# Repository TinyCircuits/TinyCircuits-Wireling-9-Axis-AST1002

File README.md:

# TinyCircuits Wireling 9-Axis
# AST1002 Rev1

The design files are located under design_files/ for the TinyCircuits AST1002 Rev 1 PCB. This is a Wireling board which measures 9 degrees of freedom (9DOF) and features the ST LSM9DS1 - a system-in-package featuring a 3D digital linear acceleration sensor, a 3D digital angular rate sensor, and a 3D digital magnetic sensor.

Format is in Cadsoft Eagle format - Eagle version 6.2 was used for the original design.

For more infomation on this, check out the product page at TinyCircuits.com

# License:

Design by TinyCircuits.
All design files are released under the Creative Commons Attribution Share-Alike 3.0 License, see the following link for details: http://creativecommons.org/licenses/by-sa/3.0

All text above must be included in any redistribution or derived design

This project uses designs and concepts developed as part of the Arduino project and the LilyPad project.  The TinyCircuits design files themselves (schematics, PCB and libraries) are not directly derived from these works' design files and have been created new, however the concepts and basic architecture behind the TinyDuino and TinyLily products are derived and we thank the hard work of the organizations below for their contributions to open-source hardware:
  
Original Arduino Uno Design by Team Arduino

LilyPad Arduino Design by Leah Buechley and Sparkfun Electronics

Please support the open-source hardware community

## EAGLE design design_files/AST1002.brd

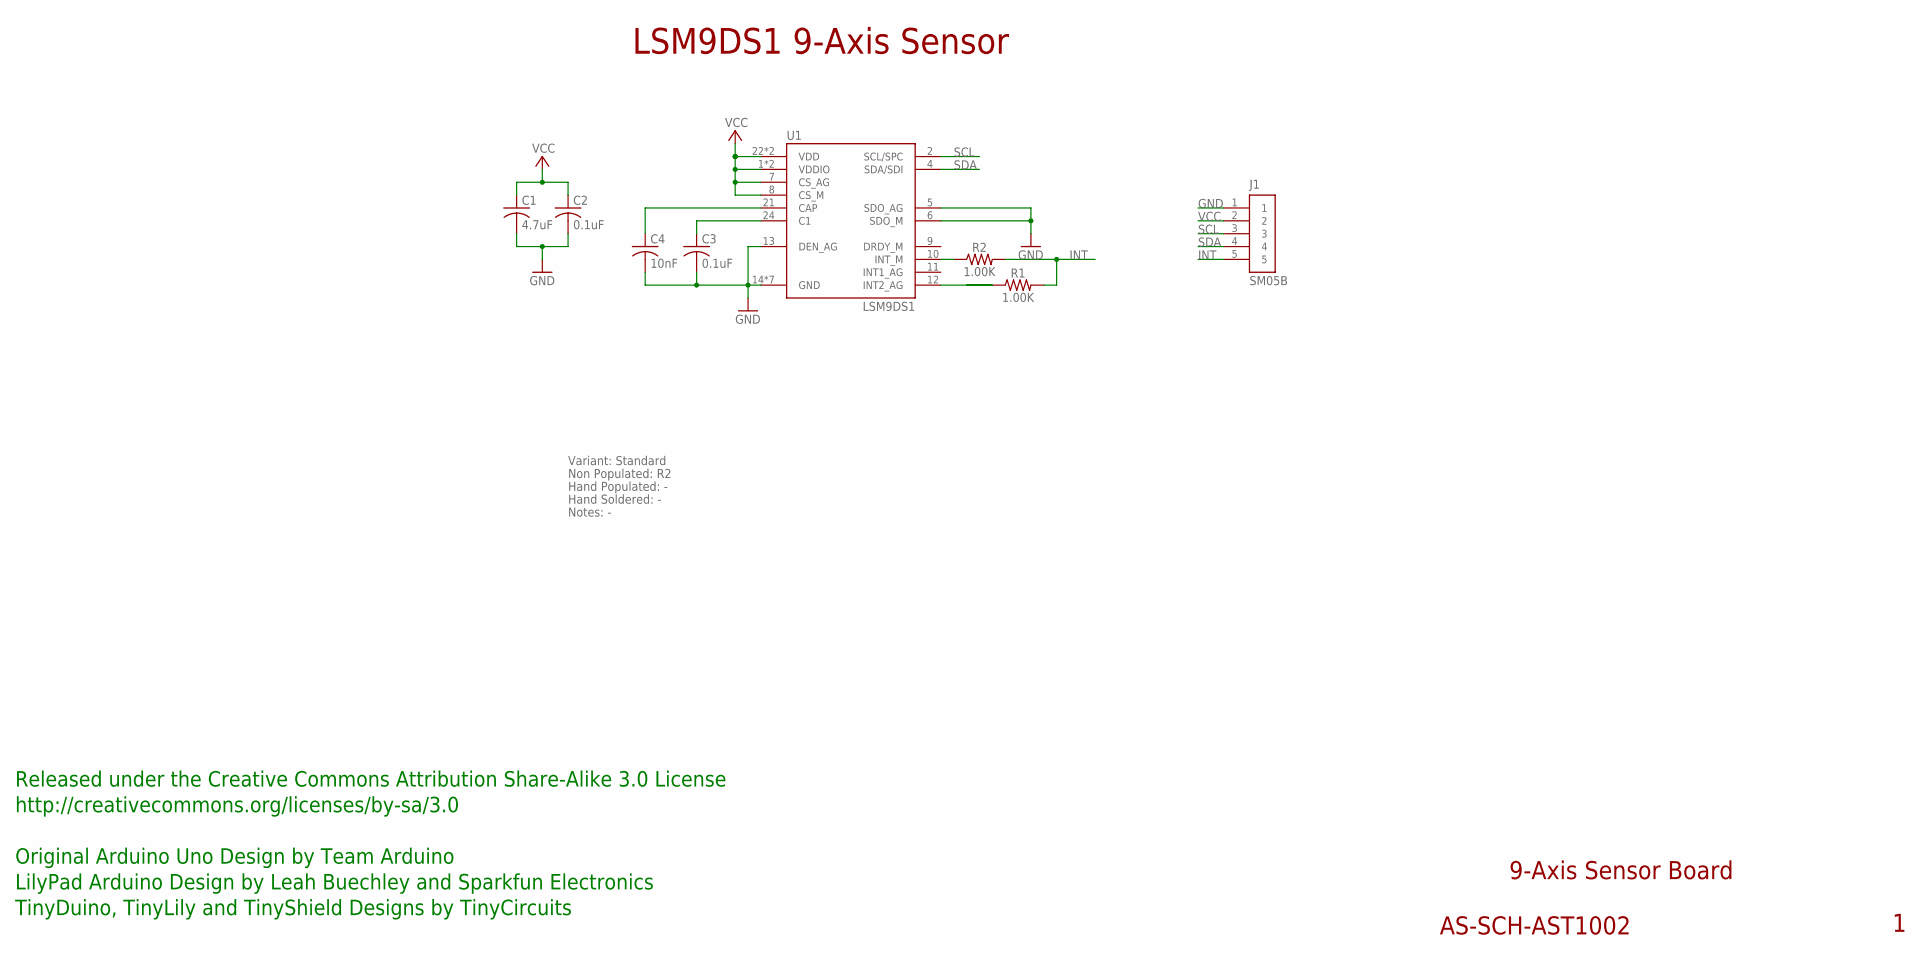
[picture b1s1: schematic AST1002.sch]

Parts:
C1: 4.7uF; C0603; PARTNO AS-ITM-00088
C2: 0.1uF; C0402
C3: 0.1uF; C0402; PARTNO AS-ITM-00008
C4: 10nF; C0402
J1: SM05B; JST_SH_5X1_EDGE
R1, R2: 1.00K; 0402; PARTNO AS-ITM-00003
U1: LSM9DS1; LGA-24

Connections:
GND: C1.2, C2.2, C3.2, C4.2, J1.1, U1.5 (SDO_AG), U1.6 (SDO_M), U1.13 (DEN_AG), U1.14 (GND), U1.15 (GND), U1.16 (GND), U1.17 (GND), U1.18 (GND), U1.19 (GND), U1.20 (GND)
INT: J1.5, R1.2, R2.2
unnamed: R1.1, U1.12 (INT2_AG)
unnamed: C3.1, U1.24 (C1)
unnamed: C4.1, U1.21 (CAP)
unnamed: R2.1, U1.10 (INT_M)
SCL: J1.3, U1.2 (SCL/SPC)
SDA: J1.4, U1.4 (SDA/SDI)
VCC: C1.1, C2.1, J1.2, U1.1 (VDDIO), U1.3 (VDDIO), U1.7 (CS_AG), U1.8 (CS_M), U1.22 (VDD), U1.23 (VDD)

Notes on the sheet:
9-Axis Sensor Board
AS-SCH-AST1002
LSM9DS1 9-Axis Sensor
Released under the Creative Commons Attribution Share-Alike 3.0 License
http://creativecommons.org/licenses/by-sa/3.0
Original Arduino Uno Design by Team Arduino
TinyDuino, TinyLily and TinyShield Designs by TinyCircuits
LilyPad Arduino Design by Leah Buechley and Sparkfun Electronics
Non Populated: R2
Hand Populated: -
Hand Soldered: -
Variant: Standard
Notes: -

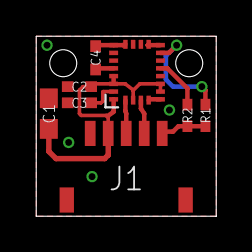
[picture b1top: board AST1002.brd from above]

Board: 2 copper layers, 10.0 x 10.0 mm, 9 parts (0 on the bottom side), 9 nets.

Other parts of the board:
U$1: DOCFIELD-TINYCIRCUITS-PCB

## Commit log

2019-08-02 added datasheet
2019-09-24 Update code
2019-12-30 updated documentation
2020-02-04 mass image update
2020-04-15 grammar fix
2020-08-14 Add CAD data
